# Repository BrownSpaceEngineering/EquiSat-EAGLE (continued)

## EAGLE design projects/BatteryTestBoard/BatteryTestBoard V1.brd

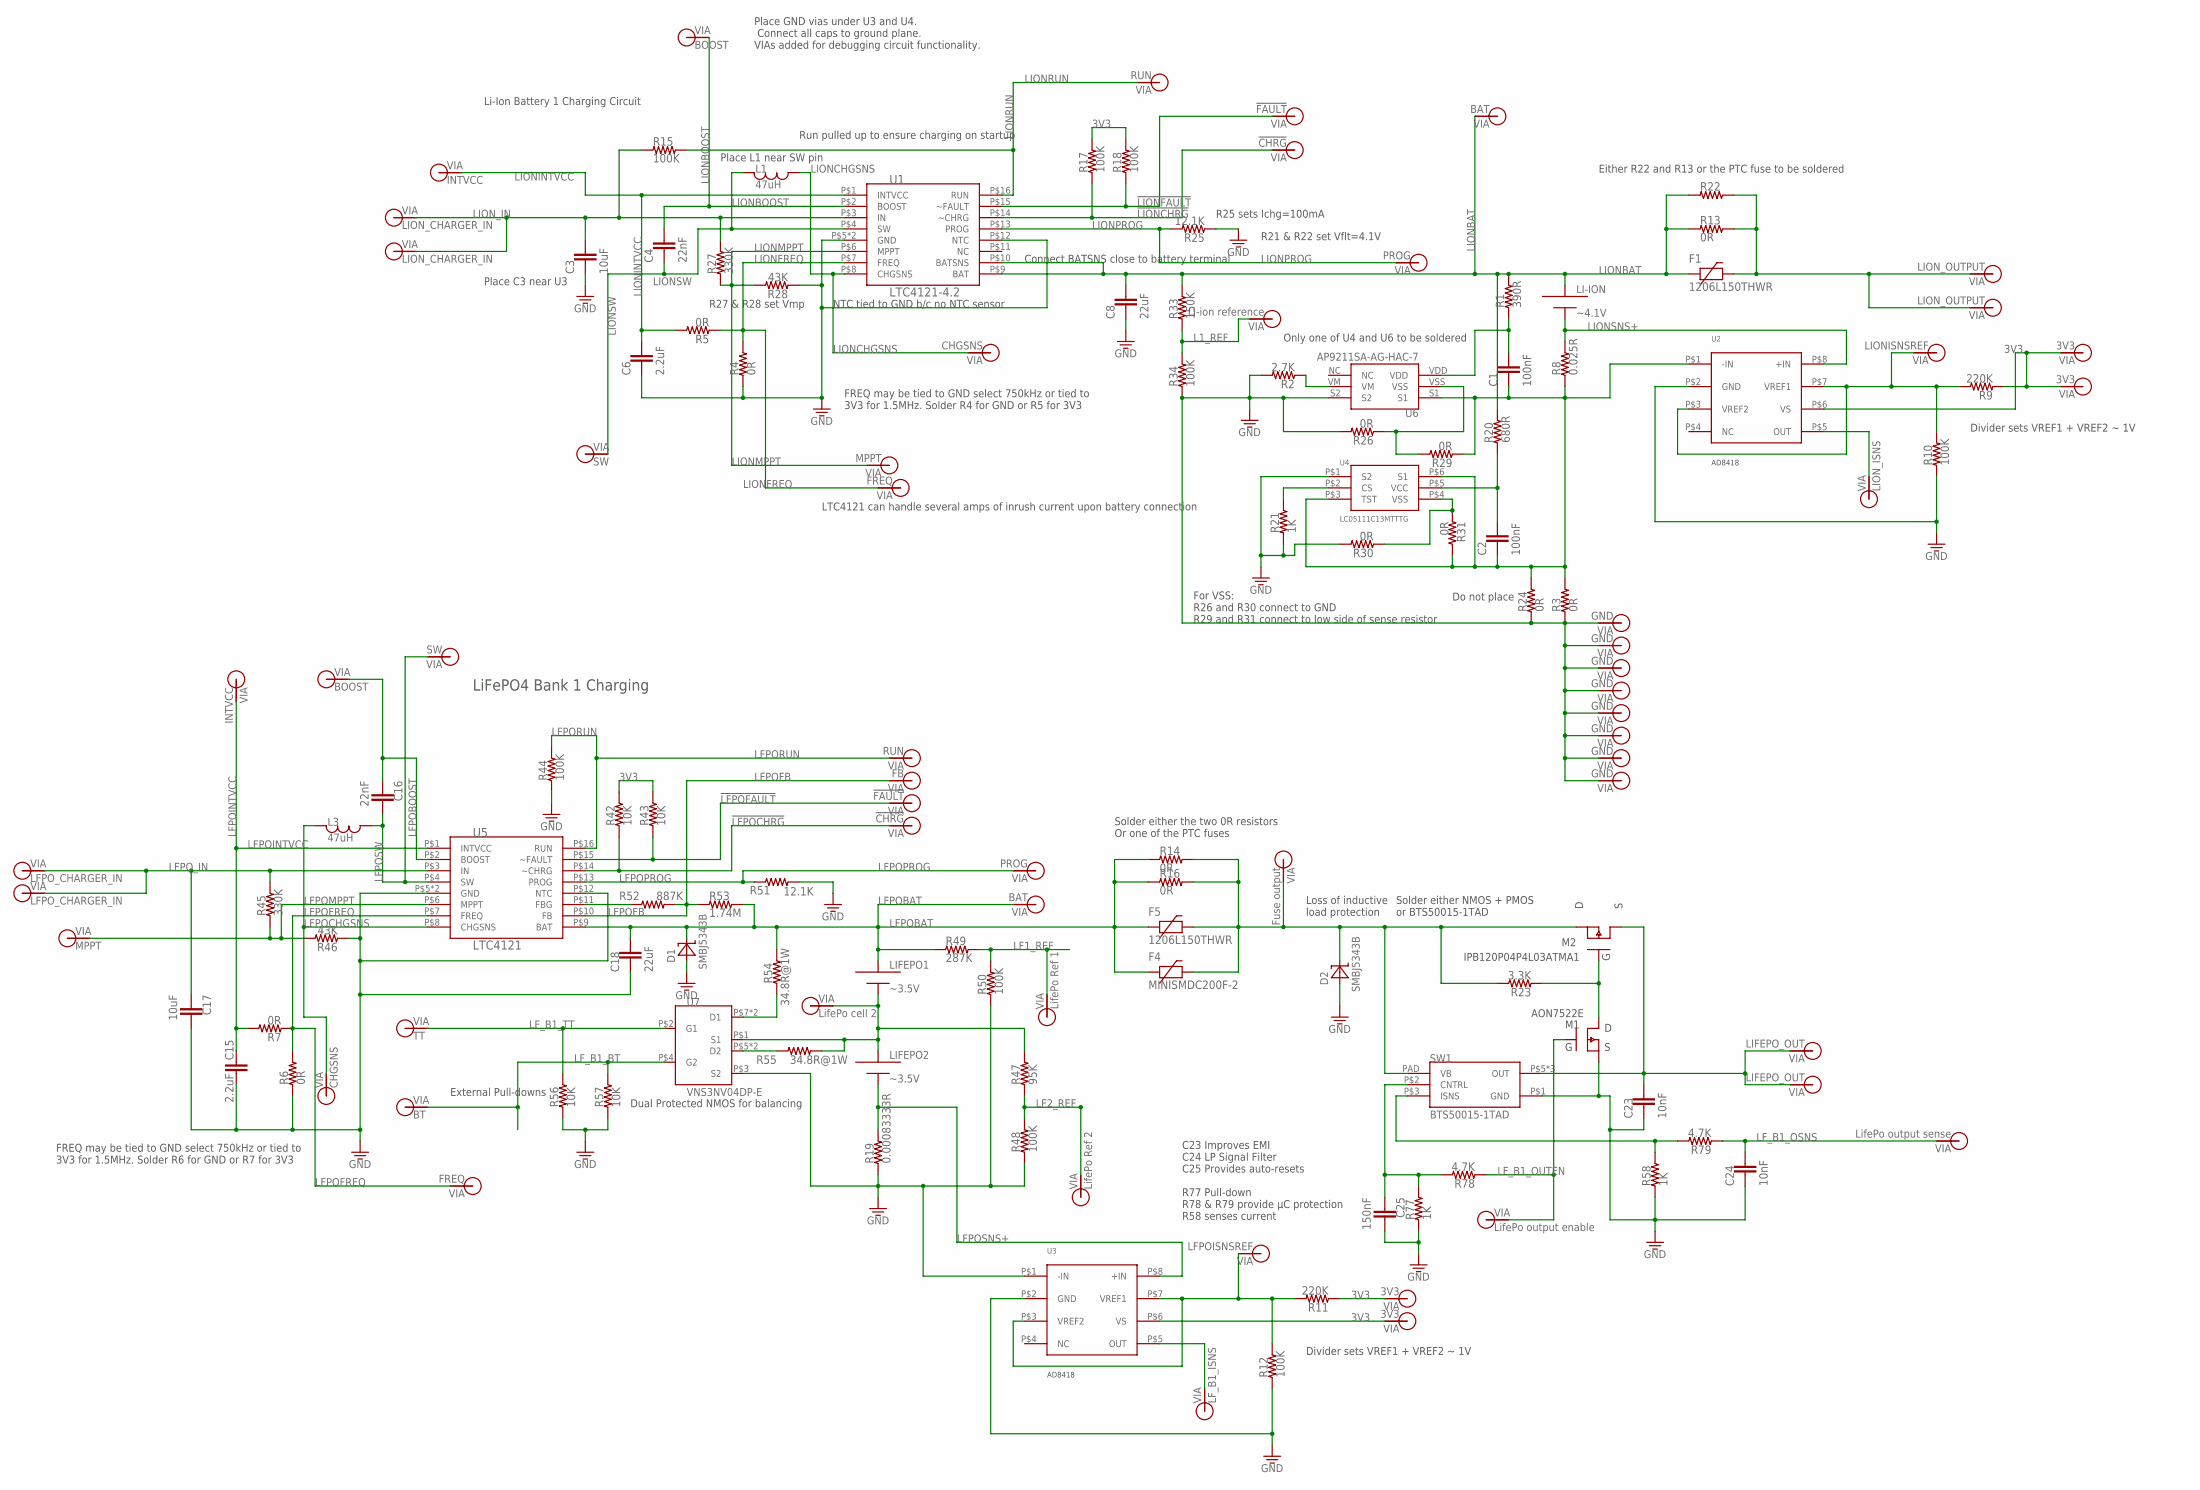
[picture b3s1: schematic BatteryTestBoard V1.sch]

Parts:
C1, C2: 100nF; 0805
C3, C17: 10uF; 0805
C4, C16: 22nF; 0805
C6, C15: 2.2uF; 0805
C8, C18: 22uF; 0805
C23, C24: 10nF; 0805
C25: 150nF; 0805
D1, D2: SMBJ5343B; DO214AA
F1, F5: 1206L150THWR; 1206
F4: MINISMDC200F-2; 1812
L1, L3: 47uH; 1812
LI-ION: ~4.1V; EQUISAT-BATTERY-VA
LIFEPO1, LIFEPO2: ~3.5V; EQUISAT-BATTERY-VA
M1: AON7522E; DFN-3X3-8
M2: IPB120P04P4L03ATMA1; TO263
R1: 390R; 0805
R2: 2.7K; 0805
R3, R13, R14, R16, R22, R24: 0R; 1210
R4, R5, R6, R7, R26, R29, R30, R31: 0R; 0805
R8: 0.025R; 1210
R9, R11: 220K; 0805
R10, R12, R15, R17, R18, R34, R44, R48, R50: 100K; 0805
R19: 0.00083333R; 1210
R20: 680R; 0805
R21, R58, R77: 1K; 0805
R23: 3.3K; 0805
R25, R51: 12.1K; 0805
R27, R45: 330K; 0805
R28, R46: 43K; 0805
R33: 150K; 0805
R42, R43, R56, R57: 10K; 0805
R47: 95K; 0805
R49: 287K; 0805
R52: 887K; 0805
R53: 1.74M; 0805
R54, R55: 34.8R@1W; 1210
R78, R79: 4.7K; 0805
SW1: BTS50015-1TAD; TO-263-7-8
U1: LTC4121-4.2; QFN-16-PAD
U2, U3: AD8418; MSOP-8
U4: LC05111C13MTTTG; WDFN6
U5: LTC4121; QFN-16-PAD
U6: AP9211SA-AG-HAC-7; U-DFN2030-6
U7: VNS3NV04DP-E; SO-8
V1, V37: LION_OUTPUT; VIA-120MIL
V2: Fuse output; VIA-60MIL-SQ
V3, V4, V5, V6, V7, V8, V10, V41: GND; VIA-60MIL-SQ
V9, V75: LFPO_CHARGER_IN; VIA-60MIL-SQ
V11: LFPOISNSREF; VIA-60MIL-SQ
V12: LIONISNSREF; VIA-60MIL-SQ
V13: LF_B1_ISNS; VIA-60MIL-SQ
V16: LifePo cell 2; VIA-60MIL-SQ
V20: LifePo output enable; VIA-60MIL-SQ
V21, V26: LIFEPO_OUT; VIA-120MIL
V29: TT; VIA-60MIL-SQ
V31: LifePo output sense; VIA-60MIL-SQ
V32: BT; VIA-60MIL-SQ
V34, V35: LION_CHARGER_IN; VIA-60MIL-SQ
V36, V54: BOOST; VIA-60MIL-SQ
V38, V57: SW; VIA-60MIL-SQ
V39, V60: MPPT; VIA-60MIL-SQ
V43: LION_ISNS; VIA-60MIL-SQ
V44: Li-ion reference; VIA-60MIL-SQ
V46, V61: CHGSNS; VIA-60MIL-SQ
V47, V62: FREQ; VIA-60MIL-SQ
V48, V63: BAT; VIA-60MIL-SQ
V50, V65: PROG; VIA-60MIL-SQ
V51, V66: !CHRG; VIA-60MIL-SQ
V52, V67: !FAULT; VIA-60MIL-SQ
V53, V68: RUN; VIA-60MIL-SQ
V55, V69: INTVCC; VIA-60MIL-SQ
V58: LifePo Ref 1; VIA-60MIL-SQ
V59: LifePo Ref 2; VIA-60MIL-SQ
V70: FB; VIA-60MIL-SQ
V71, V72, V73, V74: 3V3; VIA-60MIL-SQ

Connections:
3V3: R9.1, R11.1, R17.2, R18.2, R42.2, R43.2, U2.P$6 (VS), U3.P$6 (VS), V71.P$1, V72.P$1, V73.P$1, V74.P$1
!LFPOCHRG: R42.1, U5.P$14 (~CHRG), V66.P$1
!LFPOFAULT: R43.1, U5.P$15 (~FAULT), V67.P$1
!LIONCHRG: R17.1, U1.P$14 (~CHRG), V51.P$1
!LIONFAULT: R18.1, U1.P$15 (~FAULT), V52.P$1
FUSE_OUT: D2.C, F4.P$2, F5.2, M2.2 (D), R14.P$2 (2), R16.P$2 (2), R23.2, SW1.PAD (VB), V2.P$1
GND: C3.2, C6.2, C8.2, C15.1, C17.1, C18.2, C23.2, C24.2, C25.1, D1.A, D2.A, M1.P$1 (S), M1.P$2 (S), M1.P$3 (S), R2.2, R3.P$1 (1), R4.1, R6.1, R10.1, R12.1, R19.P$1 (1), R21.1, R24.P$1 (1), R25.1, R26.2, R28.1, R30.2, R34.1, R44.1, R46.1, R48.1, R50.1, R51.2, R56.1, R57.1, R58.1, R77.1, SW1.P$1 (GND), U1.P$5 (GND), U1.P$12 (NTC), U1.P$17 (GND), U2.P$2 (GND), U3.P$1 (-IN), U3.P$2 (GND), U4.P$1 (S2), U5.P$5 (GND), U5.P$12 (NTC), U5.P$17 (GND), U6.S2, U7.P$3 (S2), V3.P$1, V4.P$1, V5.P$1, V6.P$1, V7.P$1, V8.P$1, V10.P$1, V41.P$1
L1_REF: R33.1, R34.2, V44.P$1
L1_SNS: U2.P$5 (OUT), V43.P$1
L1_SNS1: U3.P$5 (OUT), V13.P$1
LF1_REF: R49.2, R50.2, V58.P$1
LF2_REF: R47.1, R48.2, V59.P$1
LFPOBAT: C18.1, D1.C, F4.P$1, F5.1, LIFEPO1.PLUS, R14.P$1 (1), R16.P$1 (1), R49.1, R53.2, R54.P$2 (2), U5.P$9 (BAT), V63.P$1
LFPOBOOST: C16.2, U5.P$2 (BOOST), V54.P$1
LFPOCHGSNS: L3.P$1, U5.P$8 (CHGSNS), V61.P$1
LFPOFB: R52.2, R53.1, U5.P$10 (FB), V70.P$1
LFPOFREQ: R6.2, R7.1, U5.P$7 (FREQ), V62.P$1
LFPOINTVCC: C15.2, R7.2, U5.P$1 (INTVCC), V69.P$1
LFPOMPPT: R45.1, R46.2, U5.P$6 (MPPT), V60.P$1
LFPOPROG: R51.1, U5.P$13 (PROG), V65.P$1
LFPORUN: R44.2, U5.P$16 (RUN), V68.P$1
LFPOSNS+: LIFEPO2.MINUS, R19.P$2 (2), U3.P$8 (+IN)
LFPOSW: C16.1, L3.P$2, U5.P$4 (SW), V57.P$1
LFPO_IN: C17.2, R45.2, U5.P$3 (IN), V9.P$1, V75.P$1
LF_B1_BT: R57.2, U7.P$4 (G2), V32.P$1
LF_B1_OSNS: C24.1, R79.1, V31.P$1
LF_B1_OUTEN: M1.P$4 (G), R78.1, V20.P$1
LF_B1_TT: R56.2, U7.P$2 (G1), V29.P$1
LIFE2: LIFEPO1.MINUS, LIFEPO2.PLUS, R47.2, R55.P$1 (1), U7.P$1 (S1), V16.P$1
LIONBAT: C8.1, F1.1, LI-ION.PLUS, R1.2, R13.P$1 (1), R20.2, R22.P$1 (1), R33.2, U1.P$9 (BAT), U1.P$10 (BATSNS), V48.P$1
LIONBOOST: C4.1, U1.P$2 (BOOST), V36.P$1
LIONCHGSNS: L1.P$2, U1.P$8 (CHGSNS), V46.P$1
LIONFREQ: R4.2, R5.1, U1.P$7 (FREQ), V47.P$1
LIONINTVCC: C6.1, R5.2, U1.P$1 (INTVCC), V55.P$1
LIONMPPT: R27.1, R28.2, U1.P$6 (MPPT), V39.P$1
LIONPROG: R25.2, U1.P$13 (PROG), V50.P$1
LIONRUN: R15.2, U1.P$16 (RUN), V53.P$1
LIONSNS+: LI-ION.MINUS, R8.P$2 (2), U2.P$8 (+IN)
LIONSW: C4.2, L1.P$1, U1.P$4 (SW), V38.P$1
LION_IN: C3.1, R15.1, R27.2, U1.P$3 (IN), V34.P$1, V35.P$1
LPFOFBG: R52.1, U5.P$11 (FBG)
unnamed: R2.1, U6.VM
unnamed: R11.2, R12.2, U3.P$3 (VREF2), U3.P$7 (VREF1), V11.P$1
unnamed: F1.2, R13.P$2 (2), R22.P$2 (2), V1.P$1, V37.P$1
unnamed: R26.1, R29.2, U6.VSS
unnamed: C1.1, R1.1, U6.VDD
unnamed: C23.1, M2.3 (S), SW1.P$5 (OUT), SW1.P$6 (OUT), SW1.P$7 (OUT), V21.P$1, V26.P$1
unnamed: M1.P$5 (D), M1.P$6 (D), M1.P$7 (D), M1.P$8 (D), M1.PAD (D), M2.1 (G), R23.1
unnamed: C2.1, R20.1, U4.P$5 (VCC)
unnamed: C1.2, C2.2, R3.P$2 (2), R8.P$1 (1), R24.P$2 (2), R29.1, R31.2, U2.P$1 (-IN), U4.P$3 (TST), U4.P$6 (S1), U6.S1
unnamed: R30.1, R31.1, U4.P$4 (VSS)
unnamed: R9.2, R10.2, U2.P$3 (VREF2), U2.P$7 (VREF1), V12.P$1
unnamed: R21.2, U4.P$2 (CS)
unnamed: R54.P$1 (1), U7.P$7 (D1), U7.P$8 (D1)
unnamed: R55.P$2 (2), U7.P$5 (D2), U7.P$6 (D2)
unnamed: C25.2, R77.2, R78.2, SW1.P$2 (CNTRL)
unnamed: R58.2, R79.2, SW1.P$3 (ISNS)

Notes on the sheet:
FREQ may be tied to GND select 750kHz or tied to 3V3 for 1.5MHz. Solder R4 for GND or R5 for 3V3
R25 sets Ichg=100mA
R21 & R22 set Vflt=4.1V
R27 & R28 set Vmp
Place C3 near U3
Place L1 near SW pin
Place GND vias under U3 and U4. Connect all caps to ground plane. VIAs added for debugging circuit functionality.
Li-Ion Battery 1 Charging Circuit
Run pulled up to ensure charging on startup
NTC tied to GND b/c no NTC sensor
LTC4121 can handle several amps of inrush current upon battery connection
LiFePO4 Bank 1 Charging
External Pull-downs
Dual Protected NMOS for balancing
Solder either the two 0R resistors Or one of the PTC fuses
C23 Improves EMI C24 LP Signal Filter C25 Provides auto-resets R77 Pull-down R78 & R79 provide µC protection R58 senses current
Divider sets VREF1 + VREF2 ~ 1V
Do not place
Only one of U4 and U6 to be soldered
Either R22 and R13 or the PTC fuse to be soldered
Connect BATSNS close to battery terminal
AON7522E
Solder either NMOS + PMOS or BTS50015-1TAD
Loss of inductive load protection
FREQ may be tied to GND select 750kHz or tied to 3V3 for 1.5MHz. Solder R6 for GND or R7 for 3V3
For VSS: R26 and R30 connect to GND R29 and R31 connect to low side of sense resistor

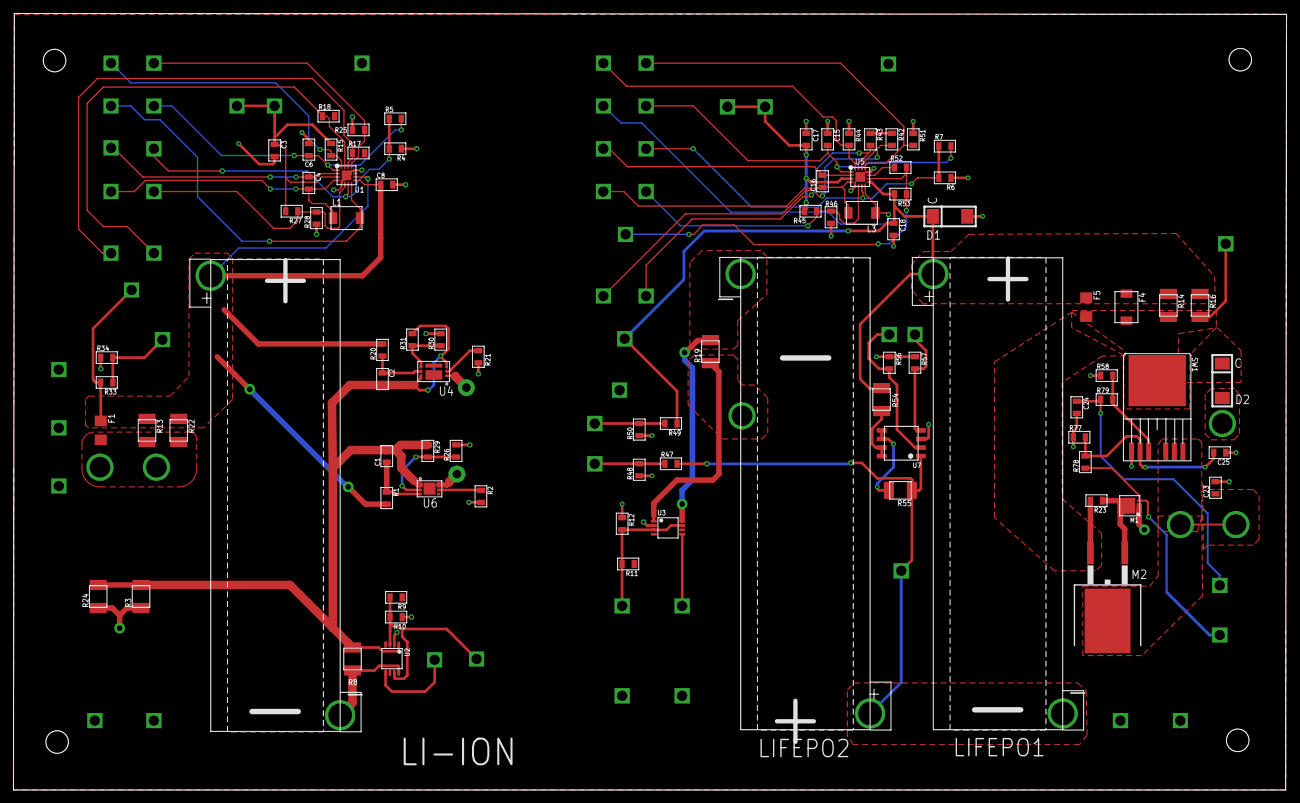
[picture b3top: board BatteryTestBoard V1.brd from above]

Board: 2 copper layers, 188.8 x 115.2 mm, 142 parts (0 on the bottom side), 57 nets.

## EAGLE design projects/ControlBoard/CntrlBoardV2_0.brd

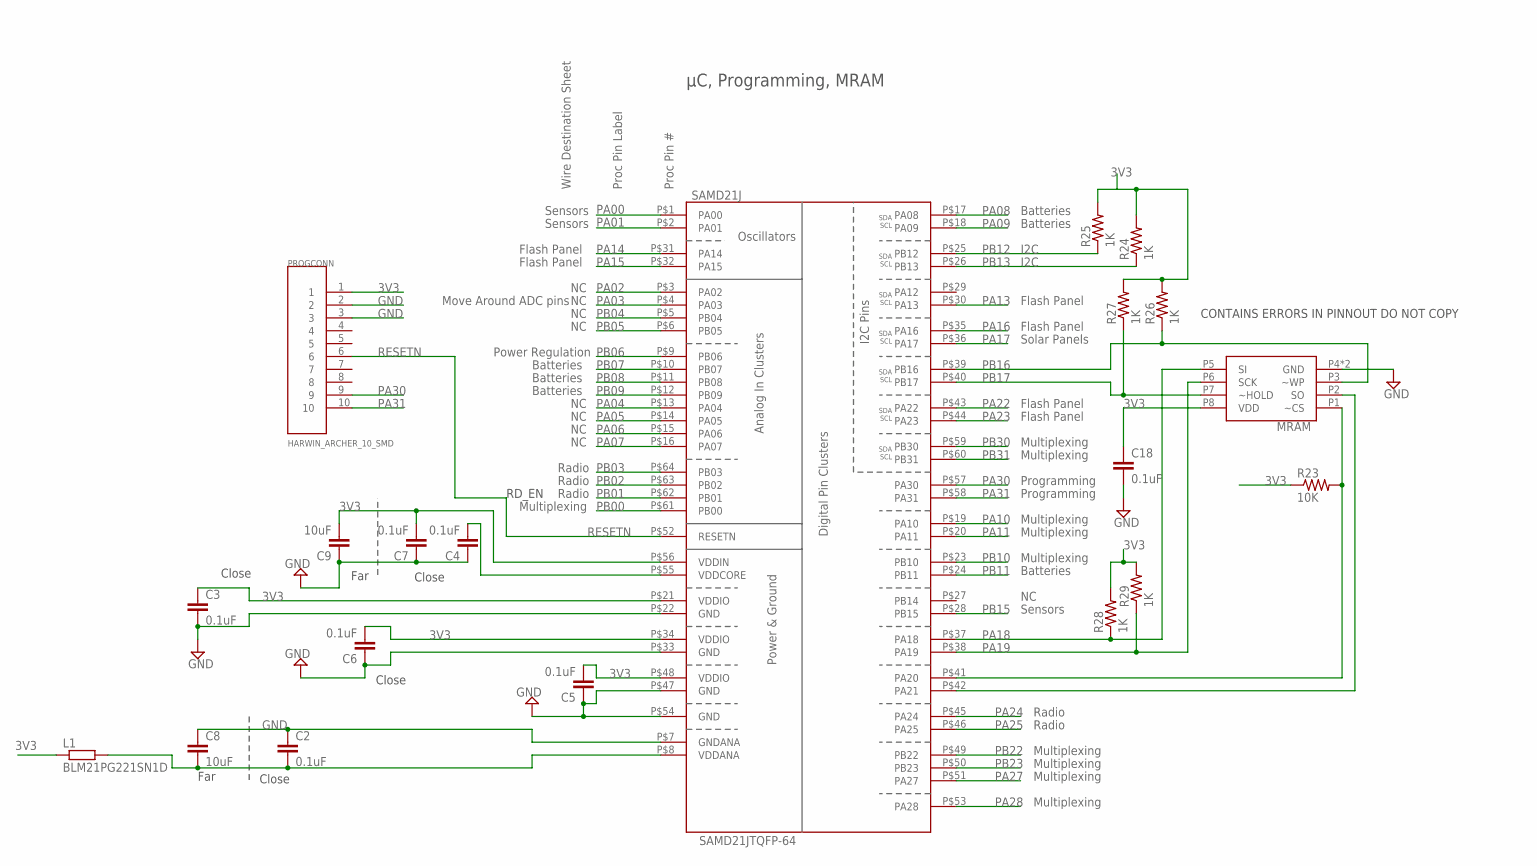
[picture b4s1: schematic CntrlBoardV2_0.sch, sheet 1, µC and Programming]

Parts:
C2, C3, C4, C5, C6, C7, C18: 0.1uF; 0805; MPN 0603YC104JAT2A
C8, C9: 10uF; 0805; MPN 08056D106KAT2A
L1: BLM21PG221SN1D; R0805; MPN BLM21PG221SN1D
MRAM: MR25H10CDC; 8PXMO-229
PROGCONN: HARWIN_ARCHER_10_SMD
R23: 10K; 0805
R24, R25, R26, R27, R28, R29: 1K; 0805
SAMD21J: SAMD21JTQFP-64; TQFP-64

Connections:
3V3: C3.1, C5.2, C6.2, C7.2, C9.2, C18.1, L1.1, MRAM.P8 (VDD), PROGCONN.1, R23.1, R24.2, R25.2, R26.2, R27.2, R28.2, R29.2, SAMD21J.P$21 (VDDIO), SAMD21J.P$34 (VDDIO), SAMD21J.P$48 (VDDIO), SAMD21J.P$56 (VDDIN); also elsewhere on the board
GND: C2.1, C3.2, C4.1, C5.1, C6.1, C7.1, C8.1, C9.1, C18.2, MRAM.P4 (GND), MRAM.P9 (GND), PROGCONN.2, PROGCONN.3, SAMD21J.P$7 (GNDANA), SAMD21J.P$22 (GND), SAMD21J.P$33 (GND), SAMD21J.P$47 (GND), SAMD21J.P$54 (GND); also elsewhere on the board
unnamed: MRAM.P1 (~CS), R23.2, SAMD21J.P$41 (PA20)
unnamed: MRAM.P2 (SO), SAMD21J.P$42 (PA21)
unnamed: C2.2, C8.2, L1.2, SAMD21J.P$8 (VDDANA)
unnamed: C4.2, SAMD21J.P$55 (VDDCORE)
PA00: SAMD21J.P$1 (PA00); also elsewhere on the board
PA01: SAMD21J.P$2 (PA01)
PA02: SAMD21J.P$3 (PA02)
PA03: SAMD21J.P$4 (PA03)
PA04: SAMD21J.P$13 (PA04)
PA05: SAMD21J.P$14 (PA05)
PA06: SAMD21J.P$15 (PA06)
PA07: SAMD21J.P$16 (PA07)
PA08: SAMD21J.P$17 (PA08); also elsewhere on the board
PA09: SAMD21J.P$18 (PA09); also elsewhere on the board
PA10: SAMD21J.P$19 (PA10); also elsewhere on the board
PA11: SAMD21J.P$20 (PA11); also elsewhere on the board
PA13: SAMD21J.P$30 (PA13); also elsewhere on the board
PA14: SAMD21J.P$31 (PA14); also elsewhere on the board
PA15: SAMD21J.P$32 (PA15); also elsewhere on the board
PA16: SAMD21J.P$35 (PA16); also elsewhere on the board
PA17: SAMD21J.P$36 (PA17); also elsewhere on the board
PA18: MRAM.P5 (SI), R28.1, SAMD21J.P$37 (PA18)
PA19: MRAM.P6 (SCK), R29.1, SAMD21J.P$38 (PA19)
PA22: SAMD21J.P$43 (PA22); also elsewhere on the board
PA23: SAMD21J.P$44 (PA23); also elsewhere on the board
PA24: SAMD21J.P$45 (PA24); also elsewhere on the board
PA25: SAMD21J.P$46 (PA25); also elsewhere on the board
PA27: SAMD21J.P$51 (PA27); also elsewhere on the board
PA28: SAMD21J.P$53 (PA28); also elsewhere on the board
PA30: PROGCONN.9, SAMD21J.P$57 (PA30); also elsewhere on the board
PA31: PROGCONN.10, SAMD21J.P$58 (PA31); also elsewhere on the board
PB00: SAMD21J.P$61 (PB00); also elsewhere on the board
PB01: SAMD21J.P$62 (PB01); also elsewhere on the board
PB02: SAMD21J.P$63 (PB02); also elsewhere on the board
PB03: SAMD21J.P$64 (PB03); also elsewhere on the board
PB04: SAMD21J.P$5 (PB04)
PB05: SAMD21J.P$6 (PB05)
PB06: SAMD21J.P$9 (PB06); also elsewhere on the board
PB07: SAMD21J.P$10 (PB07)
PB08: SAMD21J.P$11 (PB08)
PB09: SAMD21J.P$12 (PB09)
PB10: SAMD21J.P$23 (PB10); also elsewhere on the board
PB11: SAMD21J.P$24 (PB11); also elsewhere on the board
PB12: R25.1, SAMD21J.P$25 (PB12); also elsewhere on the board
PB13: R24.1, SAMD21J.P$26 (PB13); also elsewhere on the board
PB15: SAMD21J.P$28 (PB15)
PB16: MRAM.P3 (~WP), R26.1, SAMD21J.P$39 (PB16)
PB17: MRAM.P7 (~HOLD), R27.1, SAMD21J.P$40 (PB17)
PB22: SAMD21J.P$49 (PB22); also elsewhere on the board
PB23: SAMD21J.P$50 (PB23); also elsewhere on the board
PB30: SAMD21J.P$59 (PB30); also elsewhere on the board
PB31: SAMD21J.P$60 (PB31); also elsewhere on the board
RESETN: PROGCONN.6, SAMD21J.P$52 (RESETN); also elsewhere on the board

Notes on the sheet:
Close
Far
Power Regulation
Multiplexing
Radio
Sensors
Batteries
Solar Panels
I2C
Programming
Flash Panel
Proc Pin #
Proc Pin Label
Wire Destination Sheet
Move Around ADC pins
RD_EN
CONTAINS ERRORS IN PINNOUT DO NOT COPY
µC, Programming, MRAM

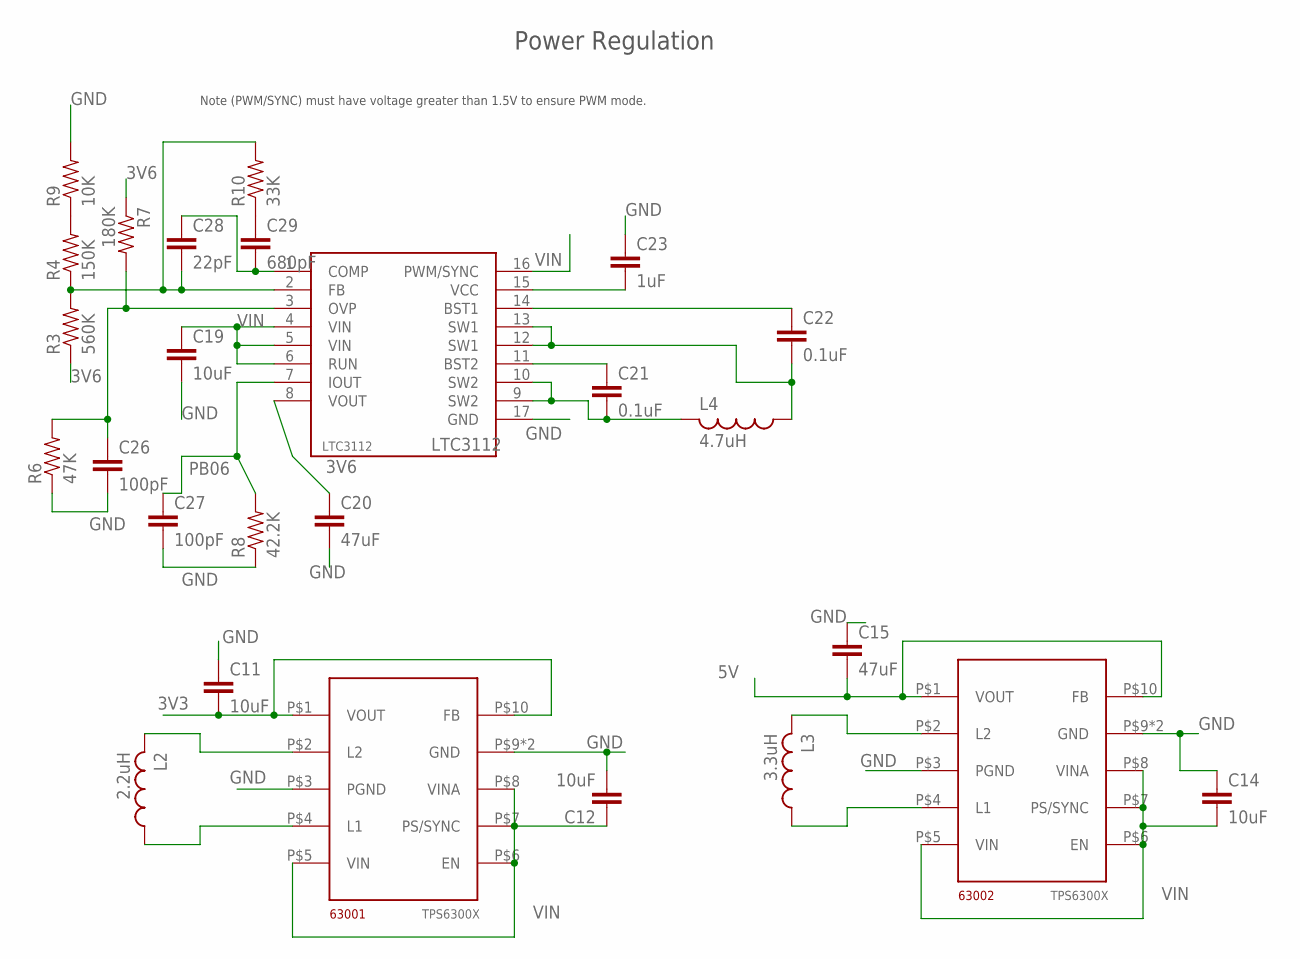
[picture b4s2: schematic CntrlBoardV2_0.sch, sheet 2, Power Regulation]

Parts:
63001, 63002: TPS6300X; QFN10_POWERPAD
C11, C12, C19: 10uF; 0603-CAP
C14: 10uF; 0603-CAP; MPN C1608X5R1A225K080AC
C15: 47uF; 0603-CAP; MPN EMK107B7474KA-T
C20: 47uF; 0805; MPN EMK107B7474KA-T
C21, C22: 0.1uF; 0603-CAP; MPN 0603YC104JAT2A
C23: 1uF; 0603-CAP
C26, C27: 100pF; 0805; MPN 08051A101J4T4A
C28: 22pF; 0805; MPN 08051A220JAT2A
C29: 680pF; 0805; MPN 08055C681KAT2A
L2: 2.2uH; L3225M
L3: 3.3uH; L3225M; MPN JMK212BJ335KG-T
L4: 4.7uH; L3225M
LTC3112: LTC3112; DHD16; MPN LTC3112EFE#PBF
R3: 560K; 0805; MPN MC01W08051560K
R4: 150K; 0805
R6: 47K; 0805
R7: 180K; 0805; MPN ERJ-6GEYJ184V
R8: 42.2K; 0805
R9: 10K; 0805
R10: 33K; 0805

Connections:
3V3: 63001.P$1 (VOUT), 63001.P$10 (FB), C11.2; also elsewhere on the board
3V6: C20.1, LTC3112.8 (VOUT), R3.1, R7.1; also elsewhere on the board
5V: 63002.P$1 (VOUT), 63002.P$10 (FB), C15.2; also elsewhere on the board
GND: 63001.P$3 (PGND), 63001.P$9 (GND), 63001.PAD (GND), 63002.P$3 (PGND), 63002.P$9 (GND), 63002.PAD (GND), C11.1, C12.2, C14.1, C15.1, C19.2, C20.2, C23.1, C26.2, C27.2, LTC3112.17 (GND), R6.1, R8.1, R9.2; also elsewhere on the board
unnamed: C21.1, LTC3112.11 (BST2)
unnamed: C22.1, LTC3112.14 (BST1)
unnamed: C23.2, LTC3112.15 (VCC)
unnamed: C22.2, L4.1, LTC3112.12 (SW1), LTC3112.13 (SW1)
unnamed: 63002.P$2 (L2), L3.2
unnamed: 63002.P$4 (L1), L3.1
unnamed: 63001.P$2 (L2), L2.2
unnamed: 63001.P$4 (L1), L2.1
unnamed: C21.2, L4.2, LTC3112.9 (SW2), LTC3112.10 (SW2)
unnamed: C28.2, LTC3112.2 (FB), R3.2, R4.1, R10.2
unnamed: C26.1, LTC3112.3 (OVP), R6.2, R7.2
unnamed: C29.1, R10.1
unnamed: C28.1, C29.2, LTC3112.1 (COMP)
unnamed: R4.2, R9.1
PB06: C27.1, LTC3112.7 (IOUT), R8.2; also elsewhere on the board
VIN: 63001.P$5 (VIN), 63001.P$6 (EN), 63001.P$7 (PS/SYNC), 63001.P$8 (VINA), 63002.P$5 (VIN), 63002.P$6 (EN), 63002.P$7 (PS/SYNC), 63002.P$8 (VINA), C12.1, C14.2, C19.1, LTC3112.4 (VIN), LTC3112.5 (VIN), LTC3112.6 (RUN), LTC3112.16 (PWM/SYNC); also elsewhere on the board

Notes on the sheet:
Note (PWM/SYNC) must have voltage greater than 1.5V to ensure PWM mode.
Power Regulation

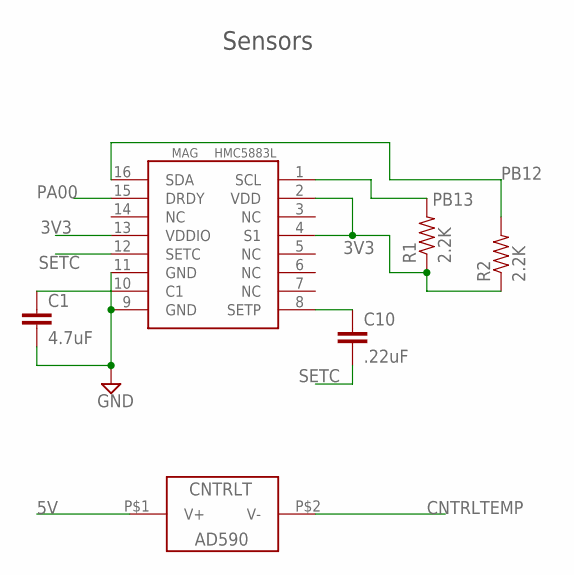
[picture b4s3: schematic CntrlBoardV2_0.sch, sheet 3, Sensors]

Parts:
C1: 4.7uF; 0805; MPN 08056D475KAT2A
C10: .22uF; 0805; MPN 08053C224KAT2A
CNTRLT: AD590-TH; AD590TH
MAG: HMC5883L; MPN HMC5883L-TR
R1, R2: 2.2K; 0805; MPN SR1-0805-222

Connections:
3V3: MAG.2 (VDD), MAG.4 (S1), MAG.13 (VDDIO), R1.1, R2.1; also elsewhere on the board
5V: CNTRLT.P$1 (V+); also elsewhere on the board
CNTRLTEMP: CNTRLT.P$2 (V-); also elsewhere on the board
GND: C1.2, MAG.9 (GND), MAG.11 (GND); also elsewhere on the board
unnamed: C1.1, MAG.10 (C1)
unnamed: C10.1, MAG.8 (SETP)
PA00: MAG.15 (DRDY); also elsewhere on the board
PB12: MAG.16 (SDA), R2.2; also elsewhere on the board
PB13: MAG.1 (SCL), R1.2; also elsewhere on the board
SETC: C10.2, MAG.12 (SETC)

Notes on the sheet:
Sensors

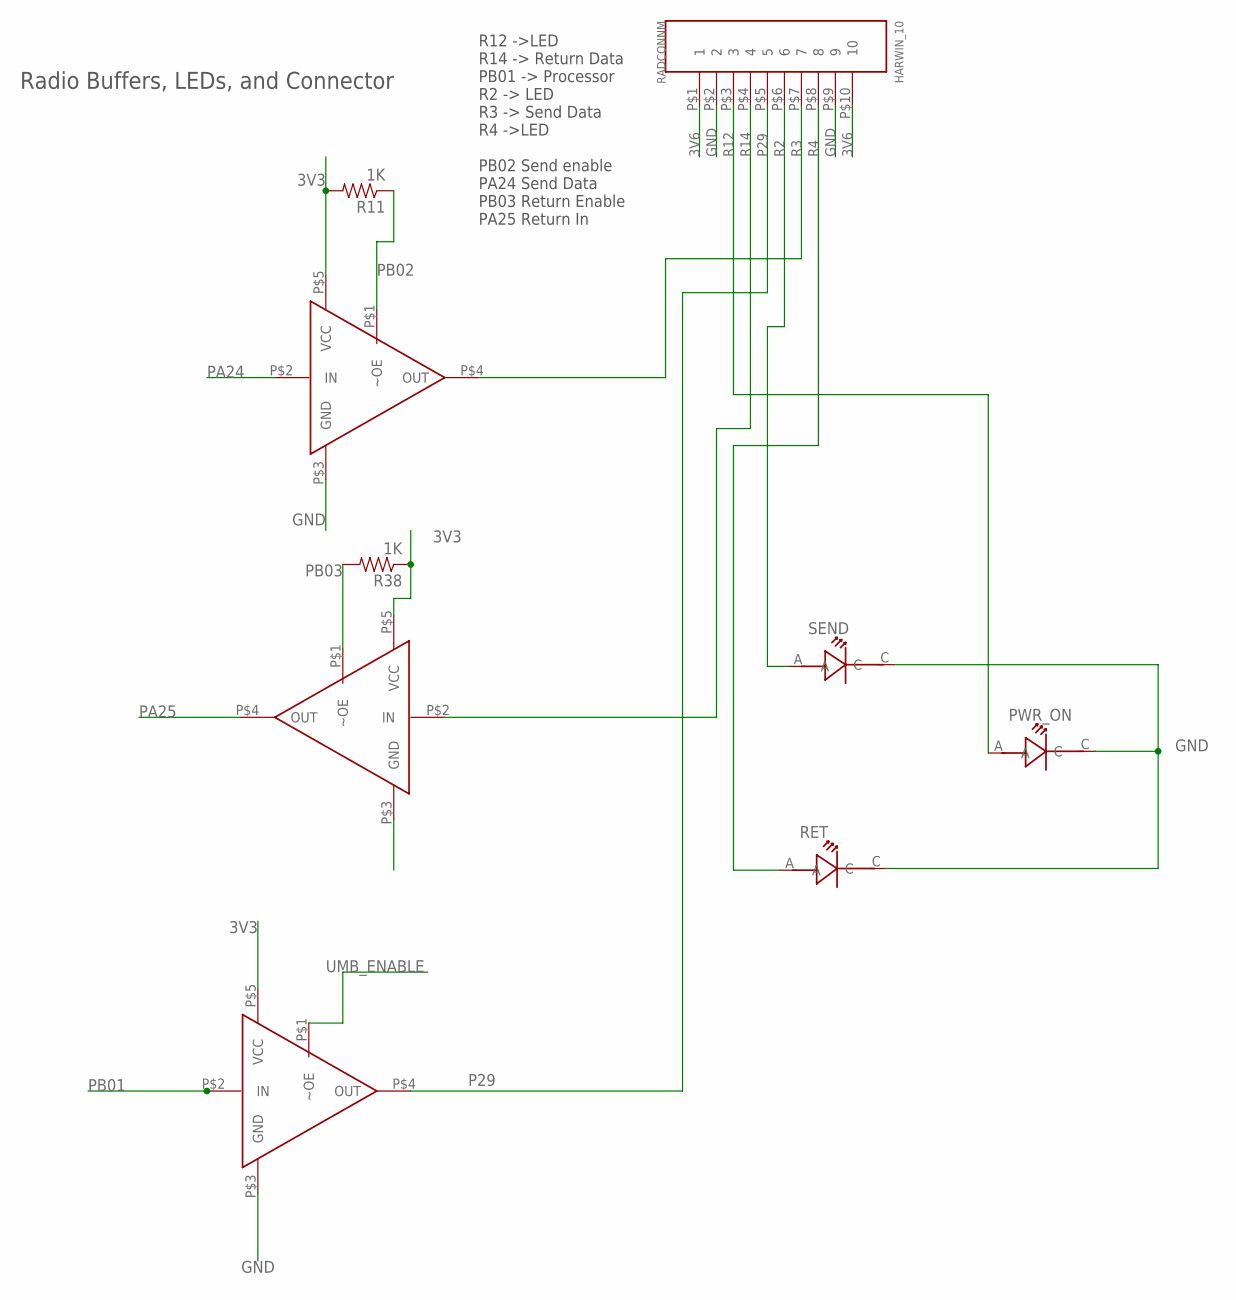
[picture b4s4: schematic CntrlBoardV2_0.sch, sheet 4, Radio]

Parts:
PWR_ON: LT-T673-Q1R2-25-Z; PLCC-2
R11, R38: 1K; 0805
RADCONNM: HARWIN_10; HARWIN_DATAMATE_10
RAD_SHDN_BUF: SN74LVC1G125; SC70
RET: LT-T673-Q1R2-25-Z; PLCC-2
RX_BUF: SN74LVC1G125; SC70
SEND: LT-T673-Q1R2-25-Z; PLCC-2
TX_BUF: SN74LVC1G125; SC70

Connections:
3V3: R11.2, R38.1, RAD_SHDN_BUF.P$5 (VCC), RX_BUF.P$5 (VCC), TX_BUF.P$5 (VCC); also elsewhere on the board
3V6: RADCONNM.P$1 (1), RADCONNM.P$10 (10); also elsewhere on the board
GND: PWR_ON.C, RADCONNM.P$2 (2), RADCONNM.P$9 (9), RAD_SHDN_BUF.P$3 (GND), RET.C, RX_BUF.P$3 (GND), SEND.C, TX_BUF.P$3 (GND); also elsewhere on the board
P29: RADCONNM.P$5 (5), RAD_SHDN_BUF.P$4 (OUT); also elsewhere on the board
PA24: TX_BUF.P$2 (IN); also elsewhere on the board
PA25: RX_BUF.P$4 (OUT); also elsewhere on the board
PB01: RAD_SHDN_BUF.P$2 (IN); also elsewhere on the board
PB02: R11.1, TX_BUF.P$1 (~OE); also elsewhere on the board
PB03: R38.2, RX_BUF.P$1 (~OE); also elsewhere on the board
R2: RADCONNM.P$6 (6), SEND.A; also elsewhere on the board
R3: RADCONNM.P$7 (7), TX_BUF.P$4 (OUT); also elsewhere on the board
R4: RADCONNM.P$8 (8), RET.A; also elsewhere on the board
R12: PWR_ON.A, RADCONNM.P$3 (3); also elsewhere on the board
R14: RADCONNM.P$4 (4), RX_BUF.P$2 (IN); also elsewhere on the board
UMB_ENABLE: RAD_SHDN_BUF.P$1 (~OE); also elsewhere on the board

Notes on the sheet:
R12 ->LED R14 -> Return Data PB01 -> Processor R2 -> LED R3 -> Send Data R4 ->LED PB02 Send enable PA24 Send Data PB03 Return Enable PA25 Return In
Radio Buffers, LEDs, and Connector

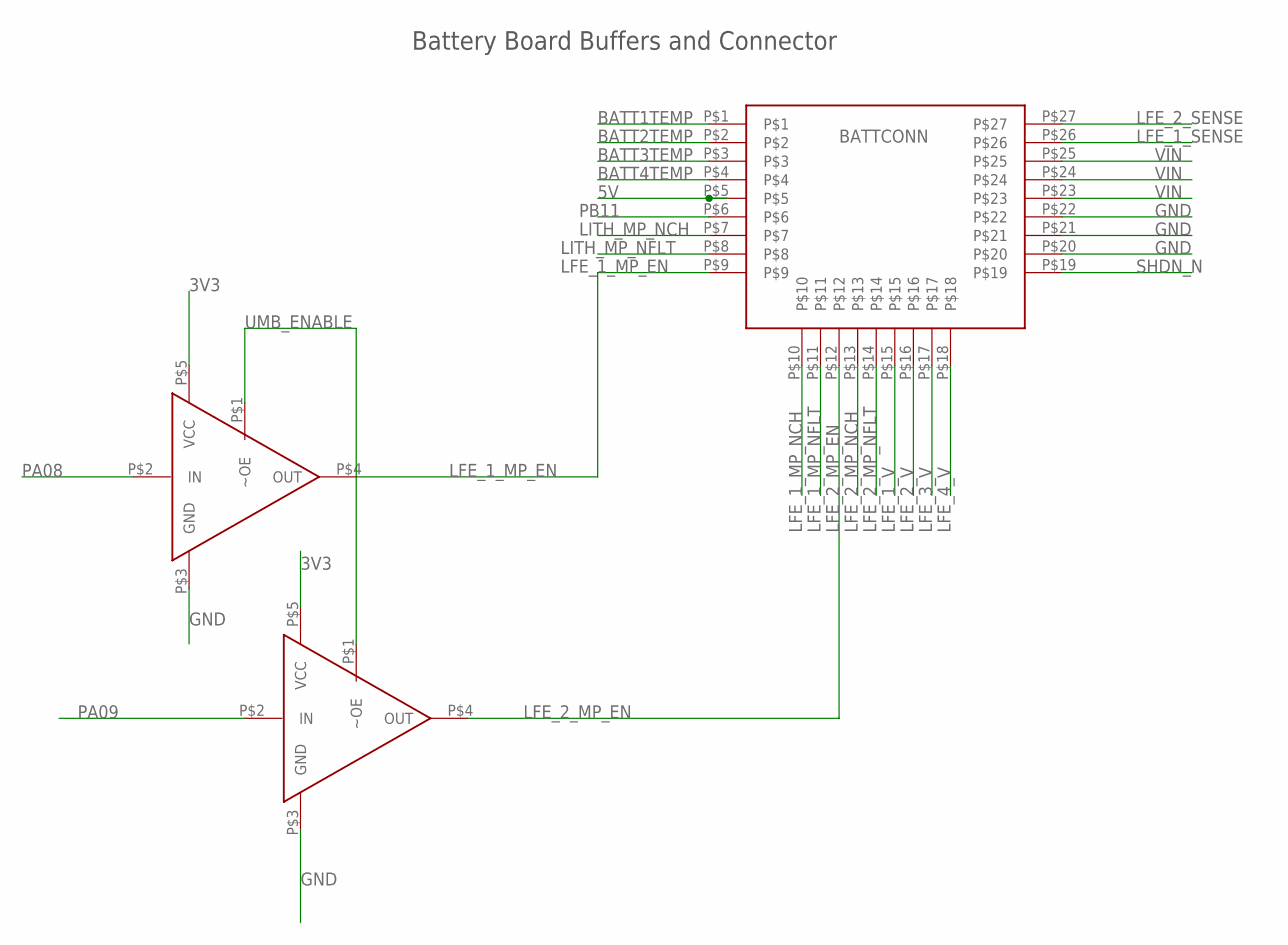
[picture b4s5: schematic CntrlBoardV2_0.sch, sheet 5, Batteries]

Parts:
BAL_1_BUF, BAL_2_BUF: SN74LVC1G125; SC70
BATTCONN: HARWIN_27; HARWIN_DATAMATE_27

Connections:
3V3: BAL_1_BUF.P$5 (VCC), BAL_2_BUF.P$5 (VCC); also elsewhere on the board
5V: BATTCONN.P$5; also elsewhere on the board
BATT1TEMP: BATTCONN.P$1; also elsewhere on the board
BATT2TEMP: BATTCONN.P$2; also elsewhere on the board
BATT3TEMP: BATTCONN.P$3; also elsewhere on the board
BATT4TEMP: BATTCONN.P$4; also elsewhere on the board
GND: BAL_1_BUF.P$3 (GND), BAL_2_BUF.P$3 (GND), BATTCONN.P$20, BATTCONN.P$21, BATTCONN.P$22; also elsewhere on the board
LFE_1_MP_EN: BAL_1_BUF.P$4 (OUT), BATTCONN.P$9
LFE_1_MP_NCH: BATTCONN.P$10; also elsewhere on the board
LFE_1_MP_NFLT: BATTCONN.P$11; also elsewhere on the board
LFE_1_SENSE: BATTCONN.P$26; also elsewhere on the board
LFE_1_V: BATTCONN.P$15; also elsewhere on the board
LFE_2_MP_EN: BAL_2_BUF.P$4 (OUT), BATTCONN.P$12
LFE_2_MP_NCH: BATTCONN.P$13; also elsewhere on the board
LFE_2_MP_NFLT: BATTCONN.P$14; also elsewhere on the board
LFE_2_SENSE: BATTCONN.P$27; also elsewhere on the board
LFE_2_V: BATTCONN.P$16; also elsewhere on the board
LFE_3_V: BATTCONN.P$17; also elsewhere on the board
LFE_4_V: BATTCONN.P$18; also elsewhere on the board
LITH_MP_NCH: BATTCONN.P$7; also elsewhere on the board
LITH_MP_NFLT: BATTCONN.P$8; also elsewhere on the board
PA08: BAL_1_BUF.P$2 (IN); also elsewhere on the board
PA09: BAL_2_BUF.P$2 (IN); also elsewhere on the board
PB11: BATTCONN.P$6; also elsewhere on the board
SHDN_N: BATTCONN.P$19; also elsewhere on the board
UMB_ENABLE: BAL_1_BUF.P$1 (~OE), BAL_2_BUF.P$1 (~OE); also elsewhere on the board
VIN: BATTCONN.P$23, BATTCONN.P$24, BATTCONN.P$25; also elsewhere on the board

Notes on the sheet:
Battery Board Buffers and Connector

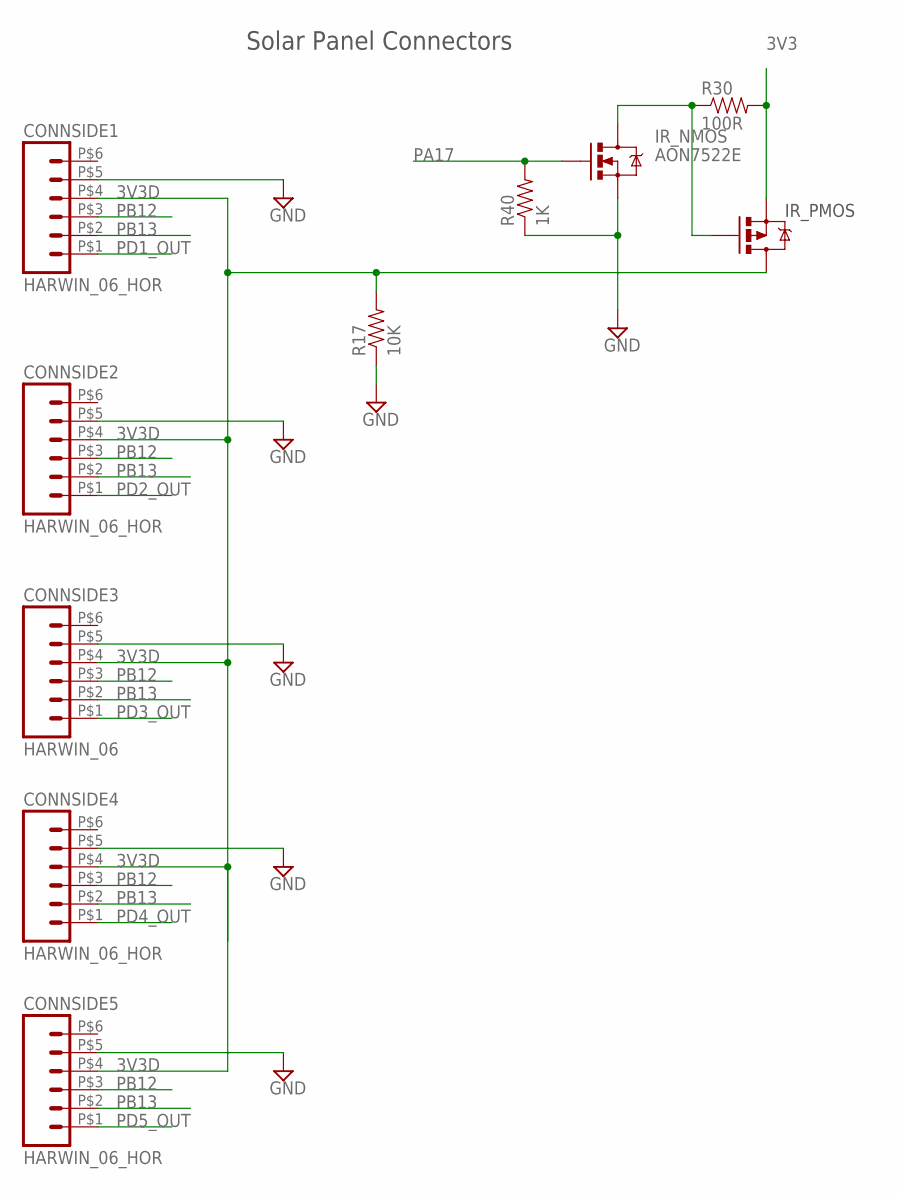
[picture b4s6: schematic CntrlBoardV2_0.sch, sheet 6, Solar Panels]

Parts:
CONNSIDE1, CONNSIDE2, CONNSIDE4, CONNSIDE5: HARWIN_06_HOR; HARWIN_DATAMATE_6_HOR
CONNSIDE3: HARWIN_06; HARWIN_DATAMATE_6
IR_NMOS: AON7522E; DFN3
IR_PMOS: POWERPMOS; SO08
R17: 10K; 0805
R30: 100R; 0805
R40: 1K; 0805

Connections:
3V3: IR_PMOS.1 (S), IR_PMOS.2 (S), IR_PMOS.3 (S), R30.2; also elsewhere on the board
3V3D: CONNSIDE1.P$4 (4), CONNSIDE2.P$4 (4), CONNSIDE3.P$4 (4), CONNSIDE4.P$4 (4), CONNSIDE5.P$4 (4), IR_PMOS.5 (D), IR_PMOS.6 (D), IR_PMOS.7 (D), IR_PMOS.8 (D), R17.2; also elsewhere on the board
GND: CONNSIDE1.P$5 (5), CONNSIDE2.P$5 (5), CONNSIDE3.P$5 (5), CONNSIDE4.P$5 (5), CONNSIDE5.P$5 (5), IR_NMOS.P$1 (S), IR_NMOS.P$2 (S), IR_NMOS.P$3 (S), R17.1, R40.1; also elsewhere on the board
IR_PW_MID: IR_NMOS.P$5 (D), IR_NMOS.P$6 (D), IR_NMOS.P$7 (D), IR_NMOS.P$8 (D), IR_NMOS.P$9 (D), IR_PMOS.4 (G), R30.1
PA17: IR_NMOS.P$4 (G), R40.2; also elsewhere on the board
PB12: CONNSIDE1.P$3 (3), CONNSIDE2.P$3 (3), CONNSIDE3.P$3 (3), CONNSIDE4.P$3 (3), CONNSIDE5.P$3 (3); also elsewhere on the board
PB13: CONNSIDE1.P$2 (2), CONNSIDE2.P$2 (2), CONNSIDE3.P$2 (2), CONNSIDE4.P$2 (2), CONNSIDE5.P$2 (2); also elsewhere on the board
PD1_OUT: CONNSIDE1.P$1 (1); also elsewhere on the board
PD2_OUT: CONNSIDE2.P$1 (1); also elsewhere on the board
PD3_OUT: CONNSIDE3.P$1 (1); also elsewhere on the board
PD4_OUT: CONNSIDE4.P$1 (1); also elsewhere on the board
PD5_OUT: CONNSIDE5.P$1 (1); also elsewhere on the board

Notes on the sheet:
IR_PMOS
Solar Panel Connectors
